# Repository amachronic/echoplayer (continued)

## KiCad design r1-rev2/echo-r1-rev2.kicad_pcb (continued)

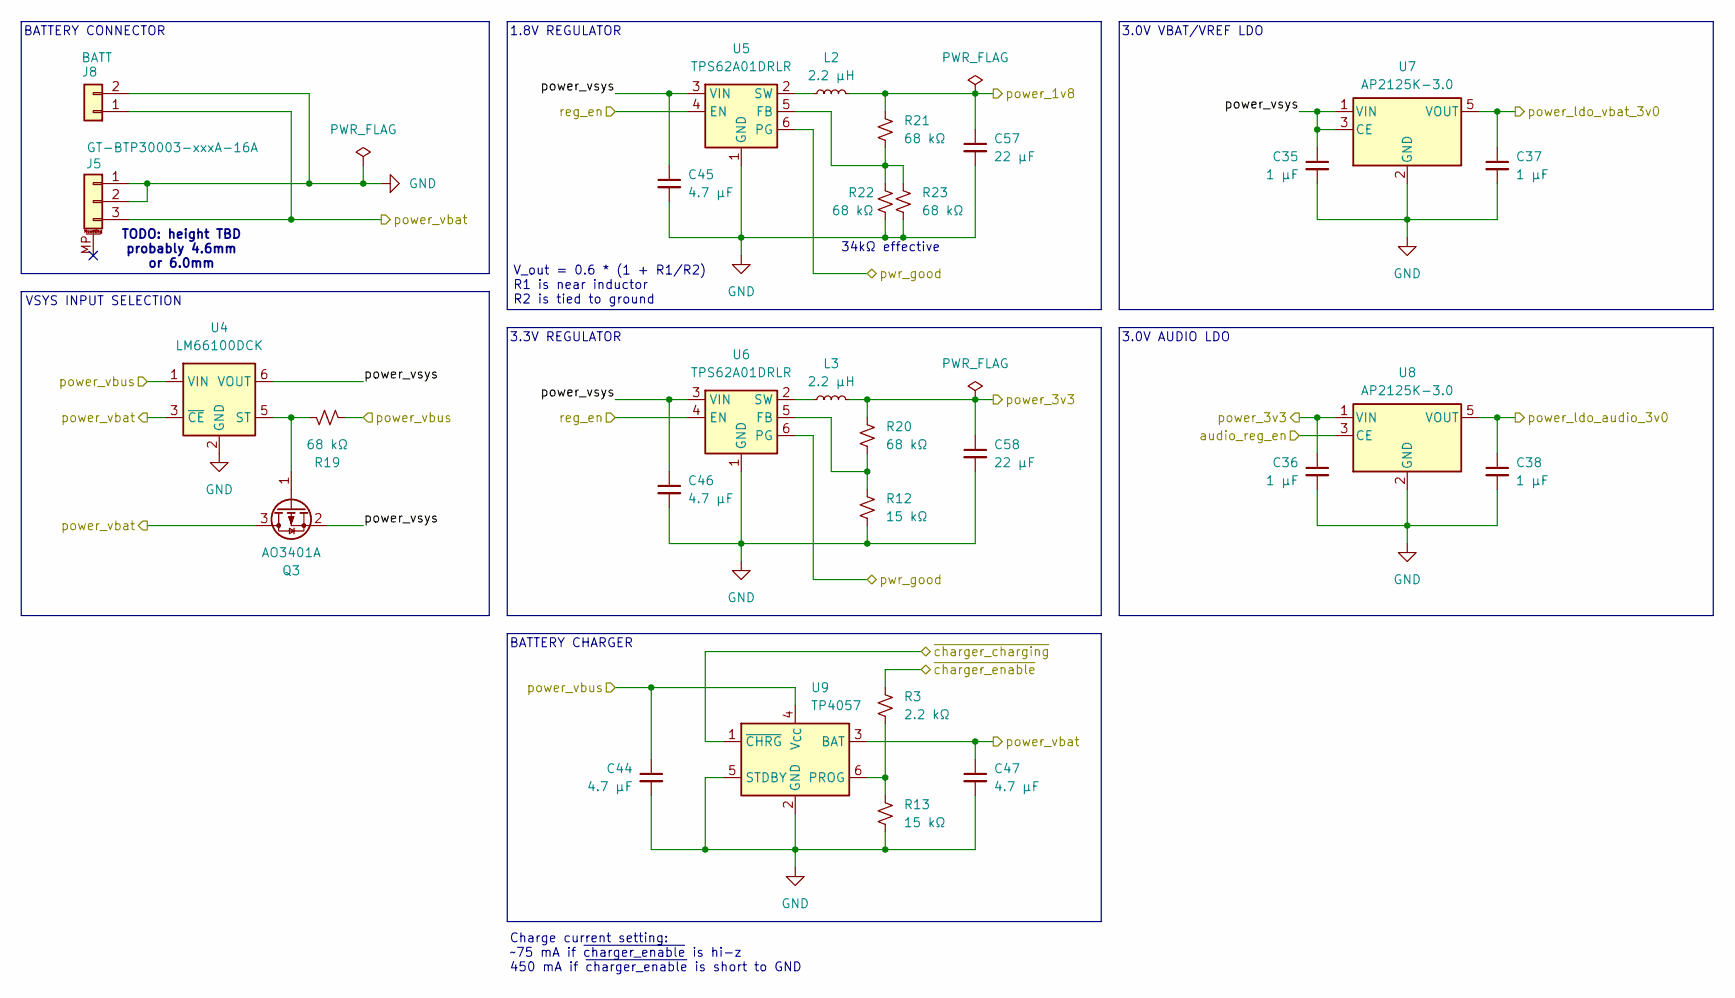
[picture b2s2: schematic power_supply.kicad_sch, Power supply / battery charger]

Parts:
C35, C36, C37, C38: 1 µF; C_0402_1005Metric
C44, C45, C46, C47: 4.7 µF; C_0805_2012Metric
C57, C58: 22 µF; C_0805_2012Metric
J5: GT-BTP30003-xxxA-16A; Conn_GT-BTP30003-xxxxA-016A
J8: BATT; PinHeader_1x02_P2.54mm_Vertical
L2, L3: 2.2 µH; L_Changjiang_FNR3015S
Q3: AO3401A; SOT-23
R3: 2.2 kΩ; R_0402_1005Metric
R12, R13: 15 kΩ; R_0402_1005Metric
R19, R20, R21, R22, R23: 68 kΩ; R_0402_1005Metric
U4: LM66100DCK; Texas_R-PDSO-G6
U5, U6: TPS62A01DRLR; SOT-563
U7, U8: AP2125K-3.0; SOT-23-5
U9: TP4057; TSOT-23-6

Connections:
+1V8: C57.1, L2.2, R21.1; also elsewhere on the board
+3V0_AUDIO: C38.1, U8.5 (VOUT); also elsewhere on the board
+3V0_VBAT: C37.1, U7.5 (VOUT); also elsewhere on the board
+3V3: C36.1, C58.1, L3.2, R20.1, U8.1 (VIN); also elsewhere on the board
/chg_charging: U9.1 (~CHRG)
/chg_enable: R3.1
/codec_avdd_en: U8.3 (CE)
/power/power_vsys: C35.1, C45.1, C46.1, Q3.2 (S), U4.6 (VOUT), U5.3 (VIN), U6.3 (VIN), U7.1 (VIN), U7.3 (CE)
/power/reg_en: U5.4 (EN), U6.4 (EN); also elsewhere on the board
/swd.nrst: U5.6 (PG), U6.6 (PG); also elsewhere on the board
GND: C35.2, C36.2, C37.2, C38.2, C44.2, C45.2, C46.2, C47.2, C57.2, C58.2, J5.1, J5.2, J8.2, R12.2, R13.2, R22.2, R23.2, U4.2 (GND), U5.1 (GND), U6.1 (GND), U7.2 (GND), U7.4 (NC), U8.2 (GND), U8.4 (NC), U9.2 (GND), U9.5 (STDBY); also elsewhere on the board
unnamed: Q3.1 (G), R19.2, U4.5 (ST)
unnamed: R21.2, R22.1, R23.1, U5.5 (FB)
unnamed: L2.1, U5.2 (SW)
unnamed: R12.1, R20.2, U6.5 (FB)
unnamed: L3.1, U6.2 (SW)
unnamed: R3.2, R13.1, U9.6 (PROG)
VBAT: C47.1, J5.3, J8.1, Q3.3 (D), U4.3 (~CE), U9.3 (BAT); also elsewhere on the board
VBUS: C44.1, R19.1, U4.1 (VIN), U9.4 (V_{CC}); also elsewhere on the board

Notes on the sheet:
TODO: height TBD probably 4.6mm or 6.0mm
3.3V REGULATOR
34kΩ effective
V_out = 0.6 * (1 + R1/R2) R1 is near inductor R2 is tied to ground
1.8V REGULATOR
Charge current setting: ~75 mA if ~{charger_enable} is hi-z 450 mA if ~{charger_enable} is short to GND
BATTERY CHARGER
BATTERY CONNECTOR
3.0V AUDIO LDO
3.0V VBAT/VREF LDO
VSYS INPUT SELECTION

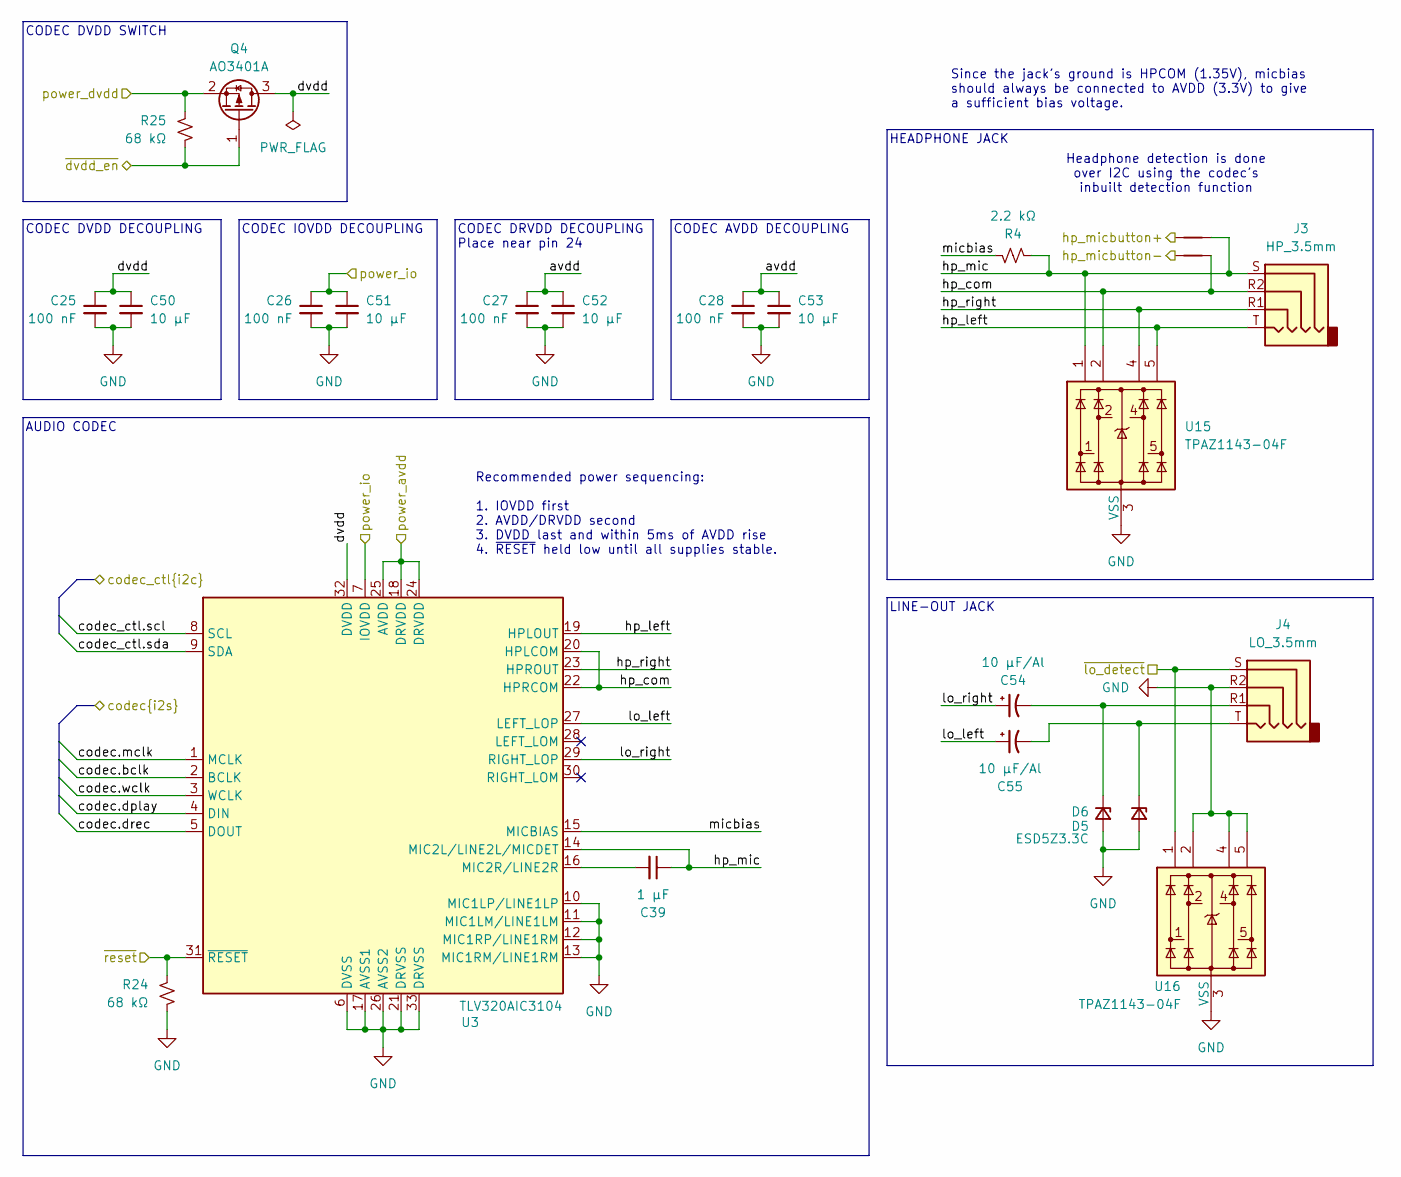
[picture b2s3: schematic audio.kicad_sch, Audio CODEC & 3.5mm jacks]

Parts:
C25, C26, C27, C28: 100 nF; C_0402_1005Metric
C39: 1 µF; C_0402_1005Metric
C50, C51, C52, C53: 10 µF; C_0805_2012Metric
C54, C55: 10 µF/Al; CP_Elec_4x5.4
D5, D6: ESD5Z3.3C; D_SOD-523
J3: HP_3.5mm; Jack_3.5mm_HCTL_HC-PJ-320A-4P-D
J4: LO_3.5mm; Jack_3.5mm_HCTL_HC-PJ-320A-4P-D
NT5, NT6: NetTie_2; NetTie_0.15mm_SMD
Q4: AO3401A; SOT-23
R4: 2.2 kΩ; R_0402_1005Metric
R24, R25: 68 kΩ; R_0402_1005Metric
U3: TLV320AIC3104; Texas_RHB0032E_VQFN-32-1EP_5x5mm_P0.5mm_EP3.45x3.45mm_Therm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
U15, U16: TPAZ1143-04F; TECHPUBLIC_UDFN-10_1.0x2.5mm_P0.5mm

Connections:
+1V8: Q4.2 (S), R25.1; also elsewhere on the board
+3V0_AUDIO: U3.18 (DRVDD), U3.24 (DRVDD), U3.25 (AVDD); also elsewhere on the board
+3V3: C26.1, C51.1, U3.7 (IOVDD); also elsewhere on the board
/audio/avdd: C27.1, C28.1, C52.1, C53.1
/audio/dvdd: C25.1, C50.1, Q4.3 (D), U3.32 (DVDD)
/audio/hp_com: J3.R2, NT6.2, U3.20 (HPLCOM), U3.22 (HPRCOM), U15.2
/audio/hp_left: J3.T, U3.19 (HPLOUT), U15.5
/audio/hp_mic: C39.1, J3.S, NT5.2, R4.2, U3.14 (MIC2L/LINE2L/MICDET), U15.1
/audio/hp_right: J3.R1, U3.23 (HPROUT), U15.4
/audio/lo_left: C55.1, U3.27 (LEFT_LOP)
/audio/lo_right: C54.1, U3.29 (RIGHT_LOP)
/audio/micbias: R4.1, U3.15 (MICBIAS)
/codec.bclk: U3.2 (BCLK); also elsewhere on the board
/codec.dplay: U3.4 (DIN); also elsewhere on the board
/codec.drec: U3.5 (DOUT); also elsewhere on the board
/codec.mclk: U3.1 (MCLK); also elsewhere on the board
/codec.wclk: U3.3 (WCLK); also elsewhere on the board
/codec_ctl.scl: U3.8 (SCL); also elsewhere on the board
/codec_ctl.sda: U3.9 (SDA); also elsewhere on the board
/codec_dvdd_en: Q4.1 (G), R25.2
/codec_reset: R24.1, U3.31 (~RESET)
/hp_micbutton+: NT5.1; also elsewhere on the board
/hp_micbutton-: NT6.1; also elsewhere on the board
/lo_detect: J4.S, U16.1
GND: C25.2, C26.2, C27.2, C28.2, C50.2, C51.2, C52.2, C53.2, D5.2 (A), D6.2 (A), J4.R2, R24.2, U3.6 (DVSS), U3.10 (MIC1LP/LINE1LP), U3.11 (MIC1LM/LINE1LM), U3.12 (MIC1RP/LINE1RM), U3.13 (MIC1RM/LINE1RM), U3.17 (AVSS1), U3.21 (DRVSS), U3.26 (AVSS2), U3.33 (DRVSS), U15.3 (VSS), U15.6 (NC), U15.7 (NC), U15.8 (VSS), U15.9 (NC), U15.10 (NC), U16.2, U16.3 (VSS), U16.4, U16.5, U16.6 (NC), U16.7 (NC), U16.8 (VSS), U16.9 (NC), U16.10 (NC); also elsewhere on the board
unnamed: C54.2, D5.1 (K), J4.R1
unnamed: C55.2, D6.1 (K), J4.T
unnamed: C39.2, U3.16 (MIC2R/LINE2R)

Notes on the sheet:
HEADPHONE JACK
CODEC AVDD DECOUPLING
CODEC DRVDD DECOUPLING Place near pin 24
Headphone detection is done over I2C using the codec's inbuilt detection function
CODEC DVDD DECOUPLING
LINE-OUT JACK
CODEC IOVDD DECOUPLING
Since the jack's ground is HPCOM (1.35V), micbias should always be connected to AVDD (3.3V) to give a sufficient bias voltage.
AUDIO CODEC
Recommended power sequencing: 1. IOVDD first 2. AVDD/DRVDD second 3. DVDD last and within 5ms of AVDD rise 4. ~{RESET} held low until all supplies stable.
CODEC DVDD SWITCH

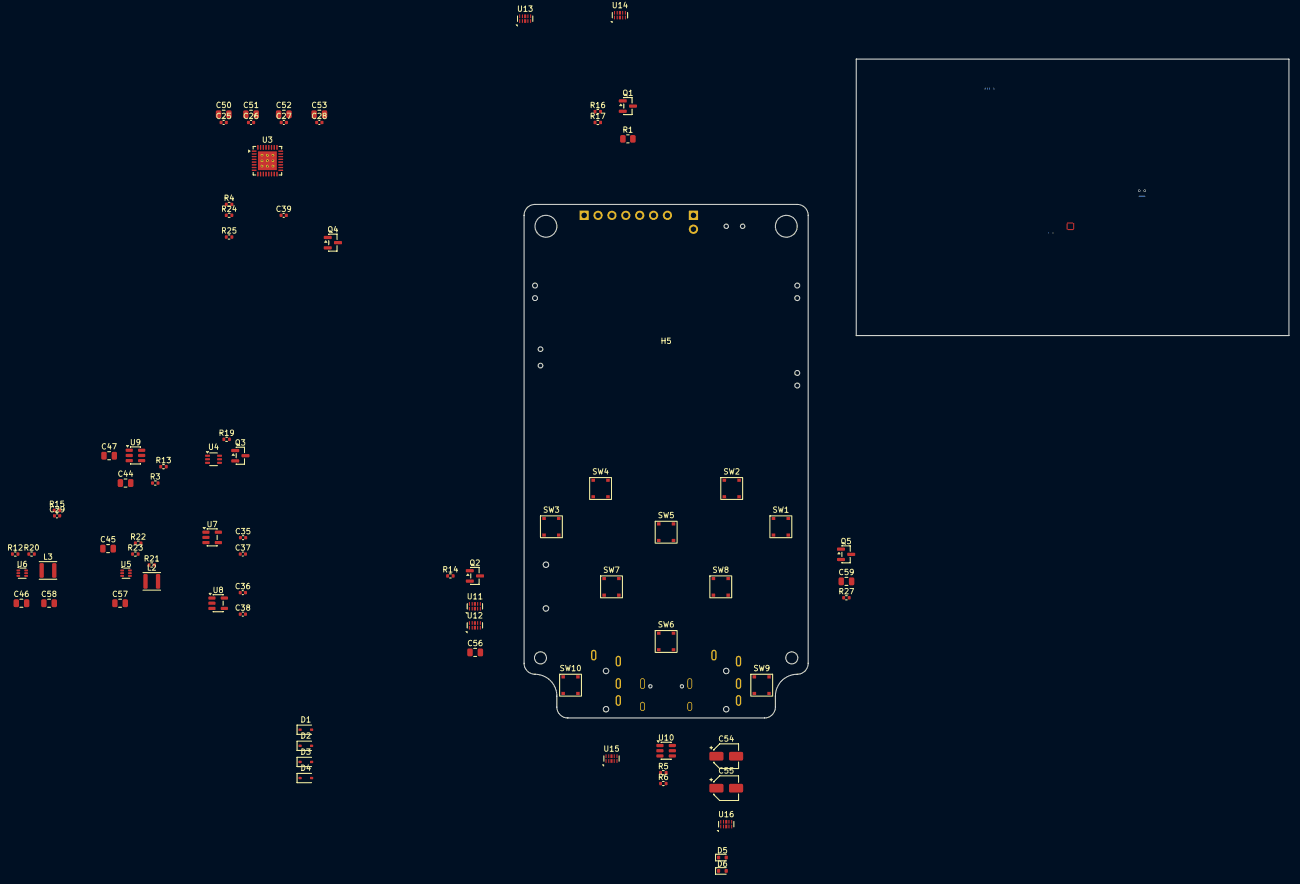
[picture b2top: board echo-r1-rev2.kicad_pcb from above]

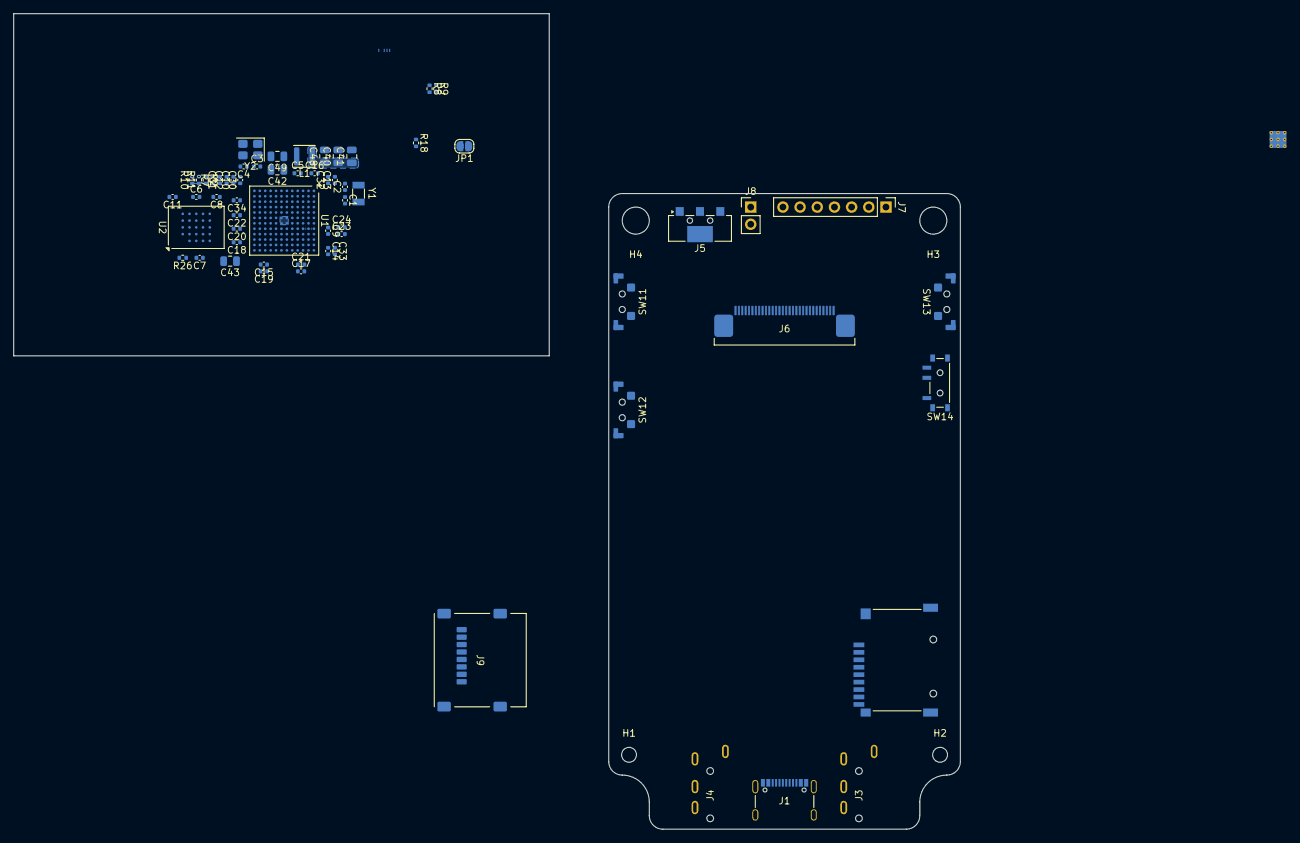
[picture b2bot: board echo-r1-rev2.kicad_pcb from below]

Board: 6 copper layers, 140.0 x 120.6 mm, 153 parts (72 on the bottom side), 111 nets.

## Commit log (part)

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2025-02-22 Initial Echo R1 release
2025-02-22 Add front/back PCB images and photo of prototype
2025-05-03 Rename case to R1-Rev1
2025-05-05 R1 case: Add holes for buttons and supports for PCB
2025-05-07 R1 case: finish most of the front side
    - Holes cut and toleranced for ports and side buttons
    - Added tolerancing on LCD module
    All the major features are now present for the front half
    of the case, although there's still nothing to affix the
    two halves of the case together (the back still needs to
    be modeled, but it will be a lot simpler than the front).
2025-05-08 Update README with latest status and known issues
2025-05-08 BOM update to remove deleted components from old backlight circuit
2025-05-10 Add Winbond W958D8NBYA5I (256Mbit HyperRAM)
2025-05-10 Add pin assignment sheets for STM32H7R3Z8xx chips
2025-05-10 Continue with redesign, update and simplify schematic
    - Consolidate small sheets (ports, etc) onto one page
    - Add placeholders for STM32 external components
    - Add power switch on SD card for resetting it
    - Fix oversized input capacitors on voltage regulators
    - Get rid of unique 1M resistor used in line-out detection
    - Remove SOT23 TVS diodes (will be replaced by another package)
2025-06-11 R1-Rev1: remove VBUS discharge resistor
    This is not needed since there is a path through the ADC
    voltage divider to discharge VBUS -- and realistically
    the battery charger should also discharge VBUS even with
    no resistive path to ground.
2025-06-11 R1-Rev1: remove old backlight components from BOM
2025-06-11 Start R1-Rev2 design
2025-06-11 R1-Rev2: add Winbond W958D8NBYA5I (256Mbit HyperRAM)
2025-06-11 R1-Rev2: WIP redesign with STM32H7R3Z8J6
    The H7R3 has a bunch of features that greatly simplify the design:
    support for HyperRAM, which requires far fewer pins than SDRAM and
    is more power efficient; this frees up the FMC to interface with the
    display in 8-bit 8080 MCU mode; and there is a built-in USB HS PHY,
    removing the need for an external PHY.
    The huge reduction in signal count allows for a smaller pin count
2025-06-11 R1-Rev2: continue with redesign, update and simplify schematic
    - Consolidate small sheets (ports, etc) onto one page
    - Add placeholders for STM32 external components
    - Add power switch on SD card for resetting it
    - Fix oversized input capacitors on voltage regulators
    - Get rid of unique 1M resistor used in line-out detection
    - Remove SOT23 TVS diodes (will be replaced by another package)
2025-06-11 R1-Rev2: strip LCSC part numbers from schematic
    These will be managed in a separate BOM spreadsheet going forward.
2025-06-11 R1-Rev2: finish STM32 power supply
2025-06-11 R1-Rev2: remove bulk capacitor on RAM side of memory bus
    There is already a 1 uF on the STM32 side, having extra bulk
    capacitance is probably unnecessary considering the chips will
    be placed very close to each other.
2025-06-11 R1-Rev2: add debouncing for regulator enable signal
2025-06-11 R1-Rev2: finish STM32 pin assignment and fix ERC issues
    - Expanded LCD bus from 8 to 16 pins so it can be accessed by DMA2D.
    - Added RDX pin to LCD bus to allow read access
    - Added UART console port for easier access to debug logging
    - Shorted USB HS and FS PHYs for DFU mode support
    - Connected all GPIOs and peripheral pins
2025-06-11 R1-Rev2: add LCD backlight driver
    The LEDs in the backlight will be in series since there are only
    two pins, but it's not clear how many LEDs are there and without
    that it's not possible to set the right current limit.
2025-06-11 R1-Rev2: initial mechanical layout
    - Outline front side of case, LCD module, and cable
    - Lay out LCD, since it requires 12'oclock viewing angle a slot is
    required to thread the ribbon cable through to the back plane.
    - Place buttons, HP/LO jacks, and USB port
    - Make the power/volume buttons larger
    - Remove old button footprints
2025-06-11 R1-Rev2: update backlight driver circuit
    There are 4 LEDs in parallel in the LCD backlight, sharing the
    same cathode/anode, so the backlight can be driven with just a
    MOSFET and resistor. (A PMOS is used to avoid having to add a
    new unique component.)
2025-06-11 R1-Rev2: use FMC NAND mode for 8-bit 8080 LCD interface
    NAND mode will translate 16-bit AXI transfers into two
    8-bit FMC transfers, which allows the 8-bit LCD bus to
    work with DMA2D. The NWAIT pin does need to be "wasted"
    on a fixed 3v3 input, since the FMC expects to poll it
    (normally it would be the busy signal from a NAND chip).
    It's seems likely this can be disabled by clearing the
2025-06-11 R1-Rev2: update LDO power supplies for codec and RTC
    The codec analog supplies (AVDD/DRVDD) are now fed through
    a 3.0V LDO powered off the main 3.3V buck regulator, which
    improves worst case efficiency from ~78% to around 86% and
    avoids stability issues that might occur when the battery
    gets within the dropout voltage range.
    The new LDO (AP2125) has a very low dropout at loads well
2025-06-11 R1-Rev2: change LCD ribbon cable slot placement and size
    The LCD won't sit flat if the fat side of the cable is lying
    underneath it because there are a bunch of capacitors there.
    The cable is long enough to reach the back of the PCB though
    if the entire thing is put through a slot right underneath
    the screen, although it's annoyingly huge.
    I've removed the screw holes there since the routing becomes
2025-06-11 R1-Rev2: updates to PCB layout, add HyperRAM routing
    - Reannotate schematic and assign footprints for passives
    - First try at HyperRAM routing
    - Fixed incorrect W958D8NBYA5I pinout
2025-06-11 R1-Rev2: update USB D+/D- net ties to avoid USBHS stubs
    The USB data lines have to be routed to both HS and FS PHYs
    since only the FS PHY supports DFU mode. To minimize stub
    length in HS operation, the data lines from the connector
    should route through the FS pins first and terminate at the
    HS pins.
2025-06-11 R1-Rev2: improve reset circuit, add XSPI CS pullup
    Connect NRST to xspi_reset and the regulator power-good signals.
    This should ensure that the STM32 and RAM will stay in reset
    until both power rails have started up. It shouldn't be necessary
    to control xspi_reset with a GPIO, but for now leave it connected
    just in case.
    The XSPI CS pin also requires an external pullup to guarantee it
2025-06-11 R1-Rev2: WIP STM32 crystal and SMPS layout
2025-06-11 R1-Rev2: move LCD in Z-axis to free up board space
    Mounting the LCD directly to the PCB just proved to be too
    awkward; mainly because the connector position made it hard
    to fit components on the upper half of the PCB. Mounting it
    on top of a 1.2mm support which directly contacts the PCB
    alleviates this, and the cable slot can now be smaller and
    moved up closer to the connector. This provides a bit more
2025-06-11 R1-Rev2: update pin assignment; add internal memory card slot
    - Removed old H743 and H7R3 LQFP144 pin assignment sheets
    - Updated pin assignments to make room for a 2nd card slot
    - Added internal memory card slot
    - Unassigned GPIOs and removed WIP routing
    - Fixed net tie reference designators
2025-06-11 R1-Rev2: fix/improve fab layer text on a few footprints
2025-06-11 R1-Rev2: add internal SD card slot footprint
2025-06-11 R1-Rev2: use LDO enable pin to control codec AVDD supply
    Now that the codec has a dedicated power supply for AVDD,
    the LDO's enable pin can be used for power sequencing.
    This eliminates a resistor and PMOS.
2025-06-11 R1-Rev2: add optional connection point for a wired battery
2025-07-09 Update README.md
    typo
2025-07-29 R1-Rev2: fix courtyards on LCD connector and TVS diodes
2025-09-02 R1-Rev2: move lcd.dcx pin to FMC_A19
    DMA2D always auto-increments the destination address, unlike
    normal DMA which has the option not to. The LCD is mapped as
    an 8-bit memory and DMA2D will perform 16-bit transfers so
    the number of pixels transferred must be <= 2**x / 2 if FMC_Ax
    is the DCX pin; otherwise the transfer will end up toggling
    DCX and won't operate correctly.
2025-09-02 R1-Rev1: add new build123d-based case [WIP]
2025-09-07 R1-Rev1: add check for battery contact spring compression
2025-09-07 R1-Rev1: fix battery thickness and increase battery box depth
2025-09-07 R1-Rev1: add screw holes for back plate attachment
2025-09-07 R1-Rev1: fix outer side wall thickness
2025-09-07 R1-Rev1: add debug header plate on back plate
2025-09-08 R1-Rev1: increase case depth to fix a couple issues
    1. Increases the thickness of the back plate around the battery;
    2. Prevents raised shadow line from hitting the LO capacitors.
2025-09-08 R1-Rev1: reinforce back plate squares to reduce deformation
2026-02-12 Restore original Rev1 schematic and PCB
    This is the first version of the hardware from before the
    Rev1.1 modifications. Has been updated to use the shared
    symbol/footprint library and stuff from the KiCAD library
    has been updated (eg. PMOS symbols renamed, and the STM32
    symbol received cosmetic changes) so it is not an exact
    match of the initial commit but the PCB layout should be
2026-02-12 Add revision suffix to KiCAD project filenames
    Makes it easier to see which version you have open.
2026-02-13 Add makefile for generating gerbers
2026-02-13 Add JLCPCB BOM/CPL generation
2026-02-13 R1-Rev2: remove outdated schematic subsheets
2026-02-15 R1-Rev1: case: fix battery thickness and increase battery box depth
2026-02-15 R1-Rev1: case: replace back plate columns with side-facing screw holes
2026-02-15 R1-Rev1: case: add shadow line on back plate
2026-02-15 R1-Rev1: case: fix outer side wall thickness
2026-02-15 R1-Rev1: case: add screw holes for back plate attachment
2026-02-15 R1-Rev1: case: move card slot to center the card
    The card sits in the connector at an offset, so the case
    slot needs to be offset from the center of the connector.
2026-02-15 R1-Rev1: pcb: fix battery positon on fab layer
2026-02-15 R1-Rev1: case: reinforce back plate squares to reduce deformation
2026-02-15 R1-Rev1: case: add side buttons
2026-02-15 R1-Rev1: case: fix clearance on battery box
    Reduce clearance around battery to ensure battery fits
    snugly and prevent losing contact.
2026-02-15 R1-Rev1: case: add start/select buttons to case
2026-02-15 R1-Rev1: case: add battery frame
2026-02-15 R1-Rev1: case: reduce thickness of corner square near power button
2026-02-15 R1-Rev1: case: add rounded sides to battery
2026-02-15 R1-Rev1: case: add side button models for power/volume buttons
2026-02-15 R1-Rev1: case: make lower shell corner squares a uniform 2.5mm thickness
    The thicker plastic doesn't really help much and one of them
    is impinging on the card connector.
2026-02-15 R1-Rev1: case: add holes for side buttons
2026-02-15 R1-Rev1: case: increase clearance of side buttons from PCB surface
    This finally gets them to work properly although they are a
    bit difficult to print.
2026-02-15 R1-Rev1: case: reinforce volume support on battery frame
2026-02-15 R1-Rev1: case: fix hole for d-pad pivot screw in battery frame
2026-03-22 Fix USB3320C ID pin
    The ID pin should be tied to VDD33 or left floating for
    device mode. Tying to ground puts the PHY into host mode,
    which requires a software workaround to get USB working.
    See Github issue: #9
2026-03-22 Fix symbol library links & resync footprints from KiCAD libraries
